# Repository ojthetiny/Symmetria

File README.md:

my shitty little keyboard designs

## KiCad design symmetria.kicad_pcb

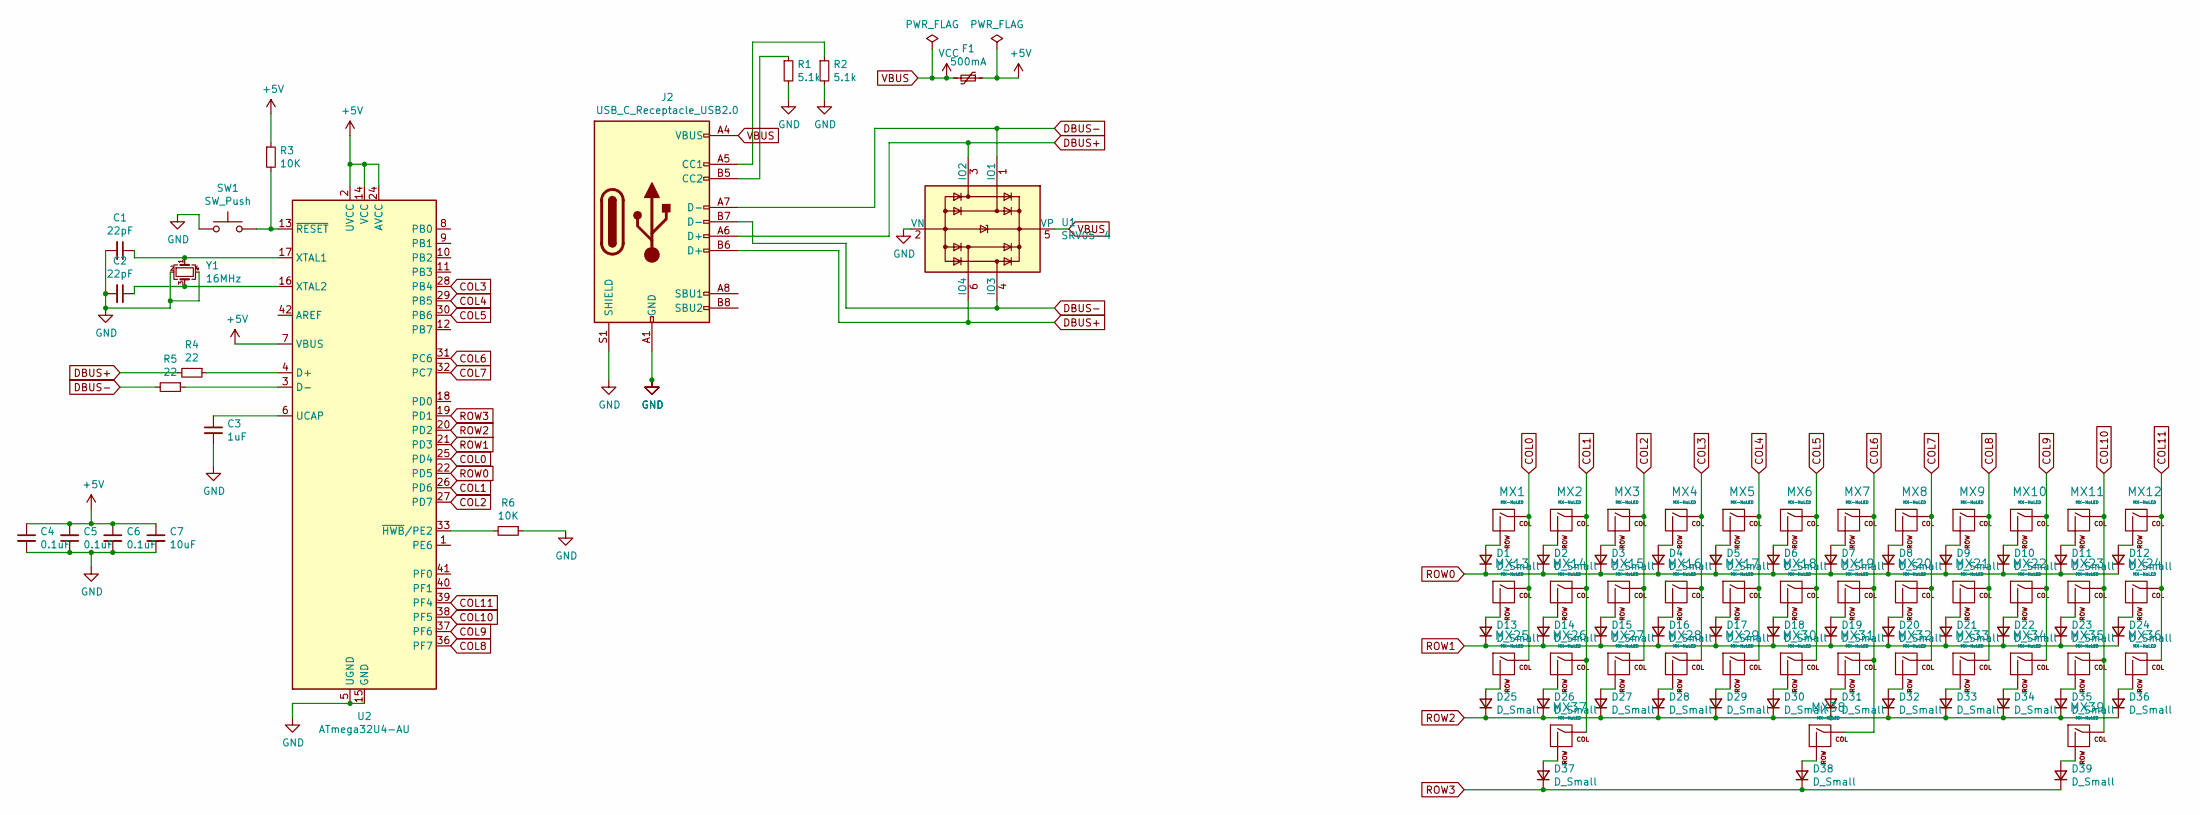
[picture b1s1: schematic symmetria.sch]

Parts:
C1, C2: 22pF; C_0805_2012Metric
C3: 1uF; C_0805_2012Metric
C4, C5, C6: 0.1uF; C_0805_2012Metric
C7: 10uF; C_0805_2012Metric
D1, D2, D3, D4, D5, D6, D7, D8, D9, D10, D11, D12, D13, D14, D15, D16, D17, D18, D19, D20, D21, D22, D23, D24, D25, D26, D27, D28, D29, D30, D31, D32, D33, D34, D35, D36, D37, D38, D39: D_Small; D_SOD-123
F1: 500mA; Fuse_1206_3216Metric
J2: USB_C_Receptacle_USB2.0; USB_C_GCT_USB4085
MX1, MX2, MX3, MX4, MX5, MX6, MX7, MX8, MX9, MX10, MX11, MX12, MX13, MX14, MX15, MX16, MX17, MX18, MX19, MX20, MX21, MX22, MX23, MX24, MX25, MX26, MX27, MX28, MX29, MX30, MX31, MX32, MX33, MX34, MX35, MX36: MX-NoLED; MXOnly-1U-NoLED
MX37, MX39: MX-NoLED; MXOnly-1.5U-NoLED
MX38: MX-NoLED; MXOnly-7U-ReversedStabilizers-NoLED
R1, R2: 5.1k; R_0805_2012Metric
R3, R6: 10K; R_0805_2012Metric
R4, R5: 22; R_0805_2012Metric
SW1: SW_Push; SKQG-1155865
U1: SRV05-4; SOT-23-6
U2: ATmega32U4-AU; TQFP-44_10x10mm_P0.8mm
Y1: 16MHz; Crystal_SMD_3225-4Pin_3.2x2.5mm

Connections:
+5V: C4.1, C5.2, C6.1, C7.1, F1.1, R3.1, U2.2 (UVCC), U2.7 (VBUS), U2.14 (VCC), U2.24 (AVCC), U2.34 (VCC), U2.44 (AVCC)
COL0: MX1.1 (COL), MX13.1 (COL), MX25.1 (COL), U2.25 (PD4)
COL1: MX2.1 (COL), MX14.1 (COL), MX26.1 (COL), MX37.1 (COL), U2.26 (PD6)
COL2: MX3.1 (COL), MX15.1 (COL), MX27.1 (COL), U2.27 (PD7)
COL3: MX4.1 (COL), MX16.1 (COL), MX28.1 (COL), U2.28 (PB4)
COL4: MX5.1 (COL), MX17.1 (COL), MX29.1 (COL), U2.29 (PB5)
COL5: MX6.1 (COL), MX18.1 (COL), MX30.1 (COL), U2.30 (PB6)
COL6: MX7.1 (COL), MX19.1 (COL), MX31.1 (COL), MX38.1 (COL), U2.31 (PC6)
COL7: MX8.1 (COL), MX20.1 (COL), MX32.1 (COL), U2.32 (PC7)
COL8: MX9.1 (COL), MX21.1 (COL), MX33.1 (COL), U2.36 (PF7)
COL9: MX10.1 (COL), MX22.1 (COL), MX34.1 (COL), U2.37 (PF6)
COL10: MX11.1 (COL), MX23.1 (COL), MX35.1 (COL), MX39.1 (COL), U2.38 (PF5); also elsewhere on the board
COL11: MX12.1 (COL), MX24.1 (COL), MX36.1 (COL), U2.39 (PF4)
DBUS+: J2.A6 (D+), J2.B6 (D+), R4.2, U1.3 (IO2), U1.6 (IO4)
DBUS-: J2.A7 (D-), J2.B7 (D-), R5.2, U1.1 (IO1), U1.4 (IO3)
GND: C1.2, C2.2, C3.2, C4.2, C5.1, C6.2, C7.2, J2.A1 (GND), J2.A12 (GND), J2.B1 (GND), J2.B12 (GND), J2.S1 (SHIELD), R1.2, R2.2, R6.1, SW1.1, U1.2 (VN), U2.5 (UGND), U2.15 (GND), U2.23 (GND), U2.35 (GND), U2.43 (GND), Y1.2, Y1.4
unnamed: C1.1, U2.17 (XTAL1), Y1.1
unnamed: C2.1, U2.16 (XTAL2), Y1.3
unnamed: C3.1, U2.6 (UCAP)
unnamed: D1.2 (A), MX1.2 (ROW)
unnamed: D2.2 (A), MX2.2 (ROW)
unnamed: D3.2 (A), MX3.2 (ROW)
unnamed: D4.2 (A), MX4.2 (ROW)
unnamed: D5.2 (A), MX5.2 (ROW)
unnamed: D6.2 (A), MX6.2 (ROW)
unnamed: D7.2 (A), MX7.2 (ROW)
unnamed: D8.2 (A), MX8.2 (ROW)
unnamed: D9.2 (A), MX9.2 (ROW)
unnamed: D10.2 (A), MX10.2 (ROW)
unnamed: D11.2 (A), MX11.2 (ROW)
unnamed: D12.2 (A), MX12.2 (ROW)
unnamed: D13.2 (A), MX13.2 (ROW)
unnamed: D14.2 (A), MX14.2 (ROW)
unnamed: D15.2 (A), MX15.2 (ROW)
unnamed: D16.2 (A), MX16.2 (ROW)
unnamed: D17.2 (A), MX17.2 (ROW)
unnamed: D18.2 (A), MX18.2 (ROW)
unnamed: D19.2 (A), MX19.2 (ROW)
unnamed: D20.2 (A), MX20.2 (ROW)
unnamed: D21.2 (A), MX21.2 (ROW)
unnamed: D22.2 (A), MX22.2 (ROW)
unnamed: D23.2 (A), MX23.2 (ROW)
unnamed: D24.2 (A), MX24.2 (ROW)
unnamed: D25.2 (A), MX25.2 (ROW)
unnamed: D26.2 (A), MX26.2 (ROW)
unnamed: D27.2 (A), MX27.2 (ROW)
unnamed: D28.2 (A), MX28.2 (ROW)
unnamed: D29.2 (A), MX29.2 (ROW)
unnamed: D30.2 (A), MX30.2 (ROW)
unnamed: D31.2 (A), MX31.2 (ROW)
unnamed: D32.2 (A), MX32.2 (ROW)
unnamed: D33.2 (A), MX33.2 (ROW)
unnamed: D34.2 (A), MX34.2 (ROW)
unnamed: D35.2 (A), MX35.2 (ROW)
unnamed: D36.2 (A), MX36.2 (ROW)
unnamed: D37.2 (A), MX37.2 (ROW)
unnamed: D38.2 (A), MX38.2 (ROW)
unnamed 57: D39.2 (A), MX39.2 (ROW); also elsewhere on the board
unnamed: J2.A5 (CC1), R2.1
unnamed: J2.B5 (CC2), R1.1
unnamed: R3.2, SW1.2, U2.13 (~RESET)
unnamed: R4.1, U2.4 (D+)
unnamed: R5.1, U2.3 (D-)
unnamed: R6.2, U2.33 (~HWB~/PE2)
ROW0: D1.1 (K), D2.1 (K), D3.1 (K), D4.1 (K), D5.1 (K), D6.1 (K), D7.1 (K), D8.1 (K), D9.1 (K), D10.1 (K), D11.1 (K), D12.1 (K), U2.22 (PD5)
ROW1: D13.1 (K), D14.1 (K), D15.1 (K), D16.1 (K), D17.1 (K), D18.1 (K), D19.1 (K), D20.1 (K), D21.1 (K), D22.1 (K), D23.1 (K), D24.1 (K), U2.21 (PD3)
ROW2: D25.1 (K), D26.1 (K), D27.1 (K), D28.1 (K), D29.1 (K), D30.1 (K), D31.1 (K), D32.1 (K), D33.1 (K), D34.1 (K), D35.1 (K), D36.1 (K), U2.20 (PD2)
ROW3: D37.1 (K), D38.1 (K), D39.1 (K), U2.19 (PD1)
VBUS: F1.2, J2.A4 (VBUS), J2.A9 (VBUS), J2.B4 (VBUS), J2.B9 (VBUS), U1.5 (VP)

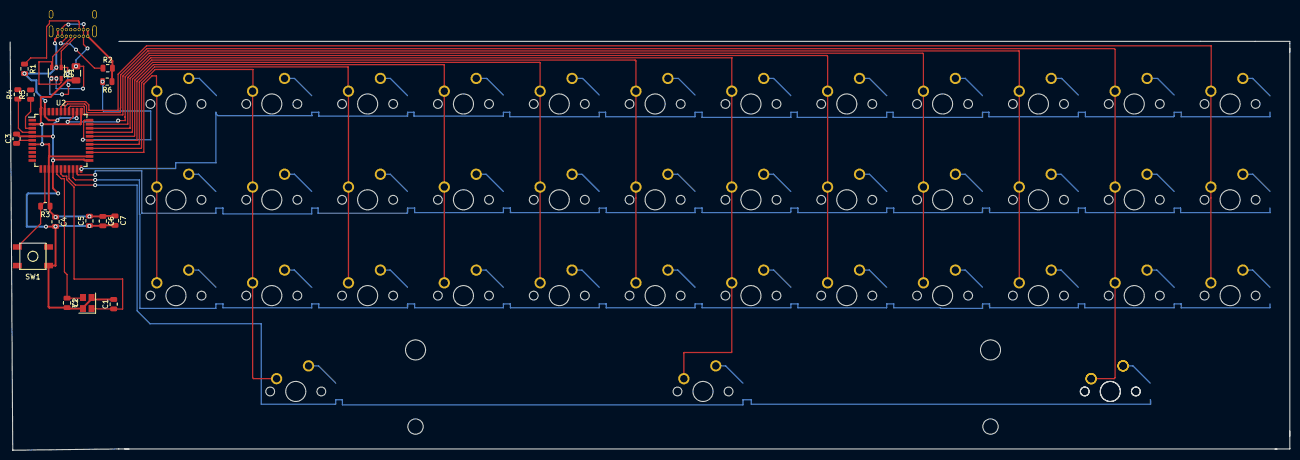
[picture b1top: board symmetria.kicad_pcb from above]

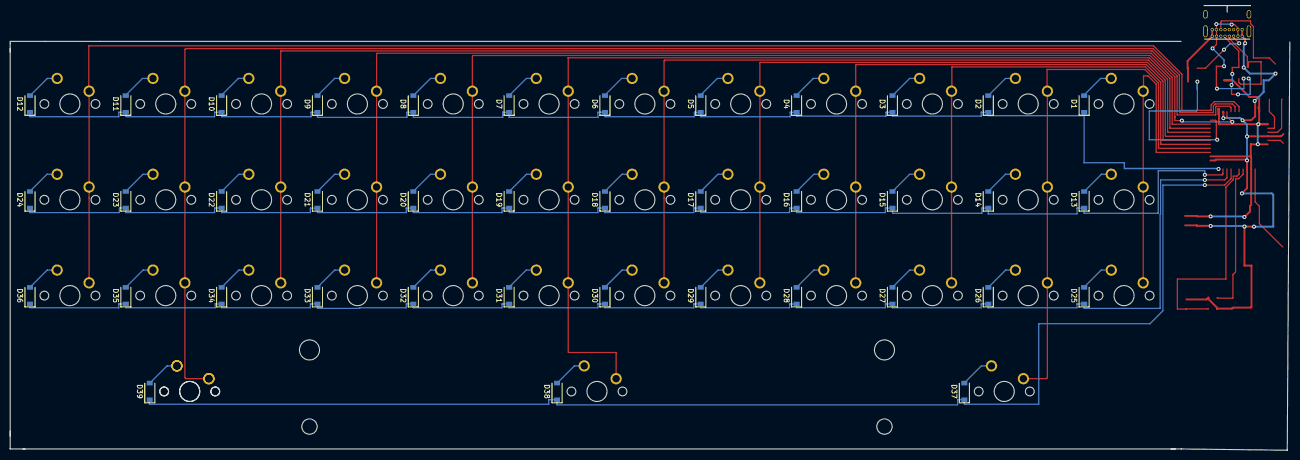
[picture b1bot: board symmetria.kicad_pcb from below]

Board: 2 copper layers, 254.4 x 81.3 mm, 98 parts (40 on the bottom side), 69 nets.

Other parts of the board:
MX39#2: MX-NoLED; MXOnly-1.5U-NoLED

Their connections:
COL10: MX39#2.1; also elsewhere on the board
unnamed 57: MX39#2.2; also elsewhere on the board

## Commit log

2020-09-08 Add Submodules
2020-09-08 Add Table Files
2020-09-08 AtMega and USB-C schematics
2020-09-08 Complete Schematics and PCB footprinting
2020-09-09 PCB Laid out
2020-09-09 Switch Tracing Complete
2020-09-09 PCB routing Finished
